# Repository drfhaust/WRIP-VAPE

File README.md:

# WRIP-VAPE
WRIST MOUNTED VAPE

# WRIP Electronics Project

This repository contains the design files for the WRIP electronics project, a wrist-mounted battery-powered vape 

## Overview

- **Design**: Wrist-mounted battery-powered vape with a refillable pod design.
- **Activation**: Breath triggered vape action.
- **Battery**: Ultrathin 250-milliampere lithium battery measuring 2.5cm by 1cm.
- **Coil**: 2-ohm nichrome wire coil designed for rapid heating.
- **Charging**: Side-mounted type-c port for rapid charging.
- **Straps**: Apple Watch style slide-in exchangeable wrist straps.
- **Indicators**: 4-stage battery level indicator.

## Hardware Specifications

- **Microcontroller**: An 8-bit microcontroller with a power level selector to fit vaping preferences.
- **LEDs**: 0-25, 25-50, 50-75, 75-100% LEDs for power level selection and battery level indication.
- **Safety**: Lithium-ion battery equipped with protection circuitry to prevent overcharge, over-discharge, short circuits, and overheating.

## Software Features

- **Display**: Shows battery level and vape power level.
- **Sleep Mode**: The device is mostly in sleep mode but wakes up at the push of a button. It stays on for 5 minutes before automatically switching off if not used.
- **Power Regulation**: Regulates power based on 58kHz PWM generated signals.

## Power Details

- **Charging**: Charges from 0-100% in 40 minutes.
- **Weight**: Weighs just 8g.
- **Discharge Rate**: Features a 15c discharge rate.
- **Dimensions**: 14mm wide, 38mm long, and 5mm thick.

## Repository Structure

- `WRIP-backups`: Directory containing backup files for the project.
- `WRIP.kicad_prl`: KiCad project related file.
- `WRIP.step`: 3D model of the project in STEP format.
- `WRIP.kicad_pro`: KiCad project file.
- `#auto_saved_files#`: Directory containing auto-saved files.
- `kicad libraries`: Directory containing KiCad libraries used in the project.
- `WRIP.kicad_sch`: KiCad schematic file.
- `WRIP.kicad_pcb`: KiCad printed circuit board (PCB) design file.
- `fp-info-cache`: Directory related to footprint information cache.

## Getting Started

1. Clone this repository.
2. Open the `WRIP.kicad_pro` file using KiCad to view the project.

## Contributing

Please read the contribution guidelines before making any changes.

## License

This project is licensed under the MIT License.

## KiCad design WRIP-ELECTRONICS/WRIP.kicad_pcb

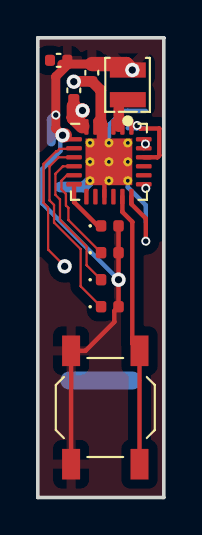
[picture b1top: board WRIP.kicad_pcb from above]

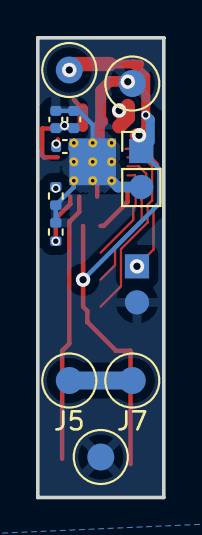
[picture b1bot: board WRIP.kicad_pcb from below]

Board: 2 copper layers, 7.0 x 25.5 mm, 22 parts (12 on the bottom side), 15 nets.

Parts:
C1, C5: 10uf; C_0402_1005Metric
C2, C3: 22uf; C_0402_1005Metric
C4, C6: 1uf; C_0402_1005Metric
D1, D2, D3, D4: LED; LED_0402_1005Metric
J1, J3: Conn_01x02_Pin; PinHeader_1x02_P2.00mm_Vertical
J4, J5, J6, J7, J8: Conn_01x01_Pin; Pin_D1.0mm_L10.0mm_LooseFit
L1: 1uh; Inductor_SMD_SUNLORD_WPN252012H
R1, R2: 100K; R_0402_1005Metric
SW1: SW_Push; SW_SPST_TL3342
U1: WQFN-24-1EP_4x4mm_P0.5mm_EP2.6x2.6mm_ThermalVias

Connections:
/5v: C4.1, U1.17 (USBOUT1), U1.18 (USBOUT1)
/coil: J5.1, J7.1
/vbat: C1.1, C5.2, D1.2 (A), D2.2 (A), D3.2 (A), D4.2 (A), J3.1, J4.1, L1.2, SW1.1, U1.1 (VBAT)
GND: C1.2, C2.2, C3.2, C4.2, C5.1, C6.2, J1.2, J3.2, J6.1, J8.1, R1.1, R2.2, U1.9 (GND), U1.22 (PGNDBST), U1.23 (PGNDBST), U1.25 (EP)
unnamed: D1.1 (K), U1.3 (LED1)
unnamed: D2.1 (K), U1.4 (LED2)
unnamed: D3.1 (K), U1.5 (LED3)
unnamed: D4.1 (K), U1.6 (LED4)
unnamed: J1.1, U1.2 (TS)
unnamed: L1.1, U1.20 (LXBST), U1.21 (LXBST)
unnamed: SW1.2, U1.11 (BUTTON)
unnamed: C2.1, C3.1, U1.16 (SWIN2), U1.19 (VMID)
unnamed: R1.2, U1.12 (TP1)
unnamed: R2.1, U1.13 (TP2)
unnamed: C6.1, U1.24 (VBUS)

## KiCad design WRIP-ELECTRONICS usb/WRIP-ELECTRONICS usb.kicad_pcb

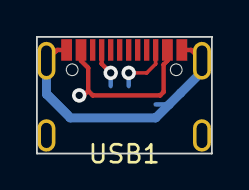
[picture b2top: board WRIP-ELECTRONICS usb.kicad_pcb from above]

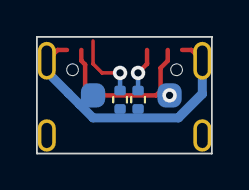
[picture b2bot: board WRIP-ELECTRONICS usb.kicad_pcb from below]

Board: 2 copper layers, 9.7 x 6.5 mm, 3 parts (2 on the bottom side), 4 nets.

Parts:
R1, R2: 5.1K; R_0402_1005Metric
USB1: USB TYPE-C CONNECTOR - HANBO - MC-107D

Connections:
/vin: USB1.A4 (VBUS), USB1.B9 (VBUS)
GND: R1.2, R2.2, USB1.A1 (GND), USB1.B12 (GND)
unnamed: R1.1, USB1.A5 (CC1)
unnamed: R2.1, USB1.B5 (CC2)

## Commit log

2023-08-10 elect
2023-10-18 latest push
